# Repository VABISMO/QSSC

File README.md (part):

# QSSC — Quantum Solid State Chip 
## Open Source Quantum Computer

A room-temperature **solid-state spin-defect** quantum platform: a Qiskit
backend, an FPGA control stack with PCB design, a validated chip-fabrication
protocol, and a web dashboard.

The qubits are **spins in NV⁻ centres in CVD diamond**, coupled by magnetic
dipole and driven by microwaves. The device operates at **~300 K** with
benchtop electronics: zero-field splitting D ≈ 2.87 GHz, ODMR readout,
64 parallel emitter and detector channels on a 20×20 mm die.

> Solid-state spin defects (NV-diamond, hBN V_B⁻, SiC V_Si) keep quantum
> coherence at **~300 K**, so the chip does not require a dilution refrigerator.
> The canonical **default** defect is the **nitrogen-vacancy (NV⁻) centre in
> CVD diamond** — the only family here whose room-temperature coherence
> (**T₂ ≈ 1.8 ms** in ¹²C-enriched diamond) is long enough to *compute*
> seriously at 300 K. Zero-field splitting **D ≈ 2.87 GHz**, room-temperature
> ODMR readout. hBN V_B⁻ and SiC V_Si are retained as **sensor variants**.

## What's in the box

| Layer | Where | Description |
|---|---|---|
| **Python core** | `qssc/` | `QSSCBackend` (Qiskit `BackendV2`), simulator, defect profiles, quantum circuits, fabrication-protocol model |
| **REST backend** | `api/` | FastAPI app exposing the simulator, ODMR model, protocol and a circuit runner |
| **Frontend** | `frontend/` | React 18 + Vite dashboard (ODMR chart, qubit grid, circuit runner, protocol viewer) |
| **FPGA RTL** | `fpga/rtl` | 11 Verilog modules (Artix-7) — UART, SPI/ADF4351 PLL, 64-ch CQD emitter drive (3× TLC5947 + `dac_ctrl` gradient DAC), detector readout (TLV9004 TIA → 4× AD7616 parallel 16-bit ADC, 1 kHz lock-in host-side), hardware QRNG (`qrng_entropy` von-Neumann extractor), command parser, top-level |
| **Hardware** | `hardware/` | KiCad boards (main control + detector head — the two sandwich boards), XDC constraints, CNC G-code, datasheets, `HARDWARE_DESIGN.md` |
| **Protocol** | `docs/FABRICATION_PROTOCOL_Diamond.md` | NV-diamond fabrication protocol: CQD emitter array, CVD diamond + NV⁻ defect engineering, on-chip photodetectors, assembly, safety |
| **Tests** | `tests/` | software/physics tests (defects, simulator, circuits, backend, API, crypto, cross-platform) — **1202 collected**, of which 1149 run in CI — plus a PCB gate track (DRC, connectivity, pin audit, routing, board integrity) that runs locally against an installed KiCad |

## Quick start

```bash
# clone, then work from the repository root (pyproject.toml lives there;
# qssc/ is the package, not a directory you cd into)
python -m venv .venv && . .venv/bin/activate
pip install -e ".[api,dev,hw]"

# run the test suite
python -m pytest --ignore-glob='tests/test_pcb_*'
#   1090 passed, 59 skipped  (see ## Testing)

# try the CLI
qssc info                              # backend / defect summary (defaults to NV)
qssc shor 15                           # → factors 3 × 5
qssc odmr                              # ODMR spectrum (NV default, dip at 2.87 GHz)

# start the REST backend (port 8011 matches the Vite dev proxy + api/main.py
# default; the Dockerfile uses PORT env, default 8000, for deploy)
uvicorn api.main:app --port 8011

# in another shell, the dashboard
cd frontend
npm install && npm run dev             # http://localhost:5173
```

## Defect platforms

| Platform | Defect | D (GHz) | T₂ @ 300 K | Readout err | Excitation | Role |
|---|---|---|---|---|---|---|
| **Diamond** | **NV⁻ (nitrogen-vacancy)** | **2.87** | **~1.8 ms\*** | **8 %** | **532 nm (green)** | **default / compute** |
| hBN | V_B⁻ (boron-vacancy) | 3.46 | ~2 µs | 12 % | 561 nm | sensor variant |
| SiC | V_Si (silicon vacancy) | 0.07 / 0.14 | ~40 µs | ~15 % | 780 nm | sensor variant |

\* The 1.8 ms **compute** figure is specific to a **bulk ¹²C-enriched CVD
diamond** plate (Balasubramanian 2009: T₂ ≈ 1.8 ms, T₁ ≈ 6 ms at 300 K;
single-qubit gate ~25 ns, two-qubit gate ~200 ns, readout ~3 µs) — long enough
to compute at room temperature. The as-built lab route instead spin-coats
**microdiamond** powder onto the carrier: those µm-scale grains host NV
ensembles with µs–tens-of-µs T₂, so the microdiamond layer is a **sensor
array**, not a compute substrate. The compute claim is scoped to the bulk-CVD
material route; both routes share the canonical 20×20 mm two-faced die (see
*Chip architecture*). hBN V_B⁻ and SiC V_Si are likewise **sensor variants**
(their T₂ is too short for serious compute at 300 K, but they sense well).

## Chip architecture

The **canonical chip is a 20×20 mm two-faced die** — 130 bond pads on a 2.5 mm
pitch (65 pads per face: 64 electrodes in an 8×8 grid + 1 common), with **no
through-silicon vias**: the emitter face and the detector face are independent
surfaces on opposite sides of the bare die. The two-board PCB sandwich (a
150×118 mm main board + a 110×102 mm head board, 6 layers each) is built
around that die — the emitter face sits in a plain through-hole 2.54 mm socket
on the main board (die removable) and the detector face plugs into the head
board's matching through-hole socket; the main board carries the FPGA, the
AD7616 readout and the TLC5947 emitter drivers. Everything below is
specified relative to that canonical die.

The chip integrates its own emitter and detector arrays and is read
**electrically**: photocurrent → transimpedance amplifier → ADC. The 64 CQD emitters (driven in
parallel by 3× TLC5947 constant-current drivers) pump the NV⁻ ensemble
(green ~520–540 nm); a resonant microwave X-gate
(2.87 GHz) flips the spin to the dark ms=±1 state; the on-chip
graphene/MoS₂ detector array measures the resulting photocurrent dip
(ODMR). A 650 nm long-pass filter blocks the green pump and passes the NV
PL (637–800 nm). Each detector electrode feeds a **TLV9004 transimpedance
amplifier** (16× quad chips), and **4× AD7616 16-bit ADCs** digitise all 64
channels (codes 0–65535) over a **9-wire SPI** bus, with **1 kHz lock-in**
demodulation host-side.

```mermaid
flowchart TB
  classDef layer fill:#16203f,stroke:#263056,color:#cfe
  classDef flow fill:#0c1430,stroke:#1d2748,color:#9fb
  classDef mw fill:#2a1530,stroke:#4a2a55,color:#f9a
  classDef elec fill:#102018,stroke:#1f4a2a,color:#9fe

  EM["**64 parallel CQD emitters (3× TLC5947)** — ITO/PEDOT:PSS/CQD-PVA/ZnO/Ag, 520–540 nm"]:::layer
  HOST["**CVD diamond spin-defect host** — NV⁻, D ≈ 2.87 GHz, T₂ ≈ 1.8 ms"]:::layer
  FILT["**650 nm long-pass filter** — blocks green pump, passes NV PL"]:::layer
  DET["**Graphene / MoS₂ photodetector array** — 64 electrodes, bias 0.1–1 V"]:::layer

  EM -- "green pump 520–540 nm (↑)" --> HOST
  HOST -- "NV PL 637–800 nm (↑)" --> FILT
  FILT -- "passes PL, blocks pump" --> DET
  DET -- "photocurrent (↓)" --> TIA["**TLV9004 TIA ×16**"]:::elec
  TIA --> ADC["**4× AD7616 16-bit ADC · 1 kHz lock-in (host)**"]:::elec
  ADC --> CTRL["**Artix-7 control FPGA** (`fpga/rtl`) — emitters, SPI, lock-in"]:::elec

  MW["**ADF4351 MW · 2.87 GHz**"]:::mw
  MW -. "resonant X-gate (phase ≈ π) → ms=±1 dark" .-> HOST
  DET -. "ODMR dip = reduced photocurrent → bit 1" .-> ADC
```

Readout: a pumped site with **no** resonant MW reads **bright** (high ADC
code, bit 0); a resonant X-gate flips the spin to **dark** (low ADC code,
ODMR dip, bit 1). Calibration drives each emitter pixel and reads all
detectors to build the emitter-pixel → detector-electrode LUT — no jig.

## Qiskit backend

`qssc.backend.QSSCBackend` is a real `BackendV2` subclass with a `Target`,
`CouplingMap`, `QubitProperties` and per-site `InstructionProperties`.
Circuits run through Qiskit Aer and return standard `get_counts()`.

Three noise modes (set via the backend `noise_mode` option):

- **`real`** (default) — the full physics path. For circuits with ≤ 10
  active qubits and no opaque compiled blocks it runs a full Aer
  density-matrix simulation with thermal + depolarizing + readout noise built
  from the defect's real T₁/T₂ and gate times (O(4ⁿ)). Larger or compiled-block
  circuits fall back to the **analytic decoherence limit** computed from the
  *same* real T₂ and gate-time parameters plus **cumulative per-gate
  depolarization**. A shared
  `signal_retention = exp(−t/T₂)·(1−d₁q)^n₁q·(1−d₂q)^n₂q`
  metric drives both the assessment and the analytic blend, so a 13-qubit Shor
  run on NV at 300 K retains ~4.7 % of the *spin* signal and still recovers the
  factors (3, 5) — NV computes at room temperature; cooling to 1 mK lifts
  retention only to ~5.5 % because NV is
  depolarization-limited, not coherence-limited.
- **`phenomenological`** (fast analytic approximation) — ideal Aer statevector +
  post-hoc per-site readout bit-flip + the same coherence×depolarization
  damping blended into the distribution. O(n) in qubits; runs in milliseconds.
- **`none`** (ideal) — noiseless statevector only.

`aer` is accepted as an alias of `real`. The phenomenological and real modes
share the *same* real T₂/gate-time parameters, so their coherence verdicts
agree — only the granularity of the noise differs.

**On-chip 2-qubit gate = spin gate (room-temperature entanglement).** The QSSC
entangles qubits with a **~200 ns microwave / magnetic-dipole spin gate**.
Spin entanglement at room temperature is documented for NV
(Neumann 2008 — electron↔nucleus; Dolde 2013 — two NV electron spins via
dipole-dipole, *Nature Physics* 9:139). Because NV's spin T₂ ≈ 1.8 ms at 300 K
≫ the 200 ns gate, the on-chip 2q gate works at room temperature and NV **computes
at 300 K** (a 13-qubit Shor-15 recovers (3, 5); a Bell pair keeps its |00⟩+|11⟩
correlations). hBN (T₂ ~ 2 µs) and SiC (~ 40 µs) are sensor variants — shallow
circuits work at 300 K, deep ones (Shor) do not. The gate fidelity is governed
by the spin T₁/T₂ + depolarization budget above (`signal_retention`).

**Per-pixel NV register (within-pixel all-to-all dipole).** The 2q gate is a
*within one microdiamond* interaction: each of the 64 die pixels holds a small
(~10 NV) register, the NVs a few nm apart, so the 1/r³ dipole couples every pair
(complete graph K_n, ODMR-frequency-addressed by one global MW antenna). The
qiskit backend (`qssc/backend.py`) simulates ONE pixel's ~10-NV register as its
circuit qubits (64×10 = 640 exceeds the 63-qubit MPS cap, so the 64 pixels are
modelled as 64 **independent** parallel processors at 300 K). Cross-pixel
coupling at the 2.5 mm pixel pitch is negligible at 300 K, so the design treats
the die as 64 independent registers. The 64-pixel hardware die (the detector
array, `/api/calibration`, the FPGA 64-channel RTL) is unchanged — `num_qubits`
≈ 10 (the register) and `pixels` = 64 (the die) now diverge. The dipole physics
is grounded in `qssc/dipole.py` (CZ gate time, addressing leakage, fidelity).

Algorithms included: **Shor** (QPE period finding), **period finding**,
**Grover search**, **Bell/GHZ**, and **quantum arithmetic** (add / sub / mul /
sqrt / log via Draper QFT adder, RGQFT multiplier and phase estimation).

### Custom Qiskit circuits

Beyond the demo algorithms, the dashboard and API accept a **user-supplied
Qiskit circuit** — either an **OpenQASM 2** string or a **Python snippet** that
builds a `QuantumCircuit` named `qc`. The builder (`qssc.build_user_circuit`)
runs the snippet in a restricted namespace (imports limited to
`qiskit` / `numpy` / `math`, no file/network/process access) and caps the
circuit at 64 qubits.

```bash
# API
curl -X POST localhost:8011/api/circuit/custom \
  -H 'Content-Type: application/json' \
  -d '{"code":"from qiskit import QuantumCircuit\nqc=QuantumCircuit(3,3)\nqc.h(0);qc.cx(0,1);qc.cx(1,2);qc.measure(range(3),range(3))","shots":512}'
```

In the dashboard, select algorithm **custom** to get a code editor with
ready-made Bell / GHZ / QFT / QASM examples.

> Security note: this is intended for a **local lab / demo tool**, not a public
> multi-tenant service. The sandbox is a restricted namespace, not a hardened
> isolation boundary.

### Environment variables

Operator-facing knobs read by the REST backend and its guards. Defaults are
what the code falls back to when the variable is unset.

| Variable | Default | Effect |
|---|---|---|
| `QSSC_API_PORT` | `8011` | Port for `uvicorn` when running `python -m api.main` directly (the Dockerfile uses `PORT`, default 8000). |
| `QSSC_RATE_LIMIT_PER_MIN` | `20` | Per-IP request budget per minute; over-budget callers get 429. |
| `QSSC_ALLOW_SYNC` | *(off)* | Set `1`/`true` to allow `?sync=true` from non-localhost. Off by default: a synchronous run blocks the single uvicorn worker (DoS vector). |
| `QSSC_TRUSTED_PROXY_CIDR` | *(empty)* | If set (e.g. `10.0.0.0/8`), the immediate peer is treated as a reverse proxy and the client IP is taken from `X-Forwarded-For`. Empty = every request is judged by its TCP peer only. |
| `QSSC_CORS_ORIGINS` | `*` | Allowed CORS origins (comma-separated for multiple). |
| `QSSC_ENABLE_CUSTOM_CIRCUIT` | `1` | `0` disables the user-supplied Qiskit-circuit endpoint (503). |
| `QSSC_CUSTOM_API_KEY` | *(empty)* | When set, `POST /api/circuit/custom` requires a matching `X-API-Key` header (401 otherwise); empty = open. |
| `QSSC_TESTING` | *(unset)* | Set to `1` by the test suite so the `TestClient` pseudo-peer counts as localhost; **leave unset in production.** |
| `QSSC_FPGA_PORT` | *(unset)* | UART device for the real board (e.g. `/dev/ttyUSB0`); unset = the stack falls back to the simulator. |
| `QSSC_FPGA_PROFILE` | `NV` | Simulation profile for the fallback `SimulatedFPGA` when no board is present. |
| `QSSC_SEED` | `42` | Seed for the simulated-FPGA RNG (reproducible sim runs). |

> The PCB-generation overrides — `QSSC_ZONE_CLEARANCE_NM`,
> `QSSC_ZONE_MIN_WIDTH_NM`, `QSSC_VIA_DIAM_NM`, `QSSC_VIA_DRILL_NM`,
> `QSSC_COPPER_GAP_NM`, `QSSC_ROUTE_DEBUG`, `QSSC_RAIL_MICRO`,
> `QSSC_STITCH_STEP`, `QSSC_PCB_PATH` — are development-time router settings
> read by `tools/route_qssc_pcb.py` and `tools/router/*` (the pour and rail
> overrides are described in
> [`hardware/HARDWARE_DESIGN.md`](hardware/HARDWARE_DESIGN.md)).

## FPGA control stack

A single **Artix-7 XC7A35T-1CSG324C** orchestrates **64 individual on-chip CQD
ASE/LED emitters** (green ~520–540 nm, constant-current-driven by 3× TLC5947
PWM drivers off a +12 V emitter rail), the **on-chip graphene/MoS₂ photodetector
array** read through 16× TLV9004 TIAs into **4× AD7616 parallel 16-bit ADCs**
with **1 kHz lock-in** demodulation host-side, an **ADF4351** microwave PLL, and
a host UART link. The chip integrates its own emitter and detector arrays and is
read electrically: the ODMR dip is a reduction of photocurrent at resonance.
The RTL ([`fpga/rtl/`](fpga/rtl), 11 modules + a self-checking
[testbench](fpga/sim/tb_top_level.v)) is **parse-verified with pyverilog,
functionally simulated with iverilog, and synthesised with yosys
`synth_xilinx` (xc7, `-abc9` pinned)** — the testbench drives
`DRIVE_EMITTER 3 100` (fires one emitter + `OK` reply),
`READ_RNG 4` (asserts the 8-hex-digit debiased word + the
`" 00064 0 0"` raw-sample stats footer) and
`READ_DETECTORS` (asserts the 64-sample stream `1234 1234 … 1234\n`,
320 bytes, 19/19 checks pass). The yosys synthesis maps the design to the
Series-7 cell library and confirms it fits the XC7A35T-1CSG324C
(**8377 LUT / 40.3 %, 7442 FF / 17.9 %, 1313 CARRY4 / 25.2 %, 9 DSP48E1 /
10.0 %, 0 inferred latches, 0 blackboxes**, 18528 tech-mapped cells — the
committed numbers live in [`fpga/synth/SYNTH_REPORT.md`](fpga/synth/SYNTH_REPORT.md)).
Synthesis runs the **staged** tree — `fpga/rtl` passed through the same patch
chain the Vivado build applies ([`fpga/synth/stage_rtl.py`](fpga/synth/stage_rtl.py)) —
so the gate measures the configuration that ships. Those three checks run in CI
**whenever `fpga/**` changes** (the FPGA job is
path-filtered: a full yosys run costs ~45 min) and locally with
`bash fpga/synth/run_synth.sh`. (A first iverilog
run caught two real handshake bugs pyverilog could not — a readout busy race and
a missing consumer-ack — now fixed.) Pin assignments live in
[`fpga/constraints.xdc`](fpga/constraints.xdc); the synthesis flow + report
live in [`fpga/synth/`](fpga/synth) (see
[`hardware/HARDWARE_DESIGN.md`](hardware/HARDWARE_DESIGN.md) §17).

### Boards

The same RTL drives both board variants — the readout goes to an external AD7616
over SPI, so nothing depends on the Xilinx XADC hard block, and only the `.xdc`
pin map changes. Toolchain for both is the free Xilinx **Vivado**; the host link
is a USB cable to the board's USB-UART bridge at **115200-8-N-1**.

| Variant | FPGA | Where | Status |
|---|---|---|---|
| **Custom QSSC PCB** | Artix-7 **XC7A35T-1CSG324C** | [`hardware/pcb/`](hardware/pcb), pins in [`fpga/constraints.xdc`](fpga/constraints.xdc) | design artefact: boards, XDC and yosys synthesis complete; bitstream packaging outstanding |
| **Home-lab QMTECH** | Artix-7 **XC7A15T** (stock dev board) | [`fpga/qmtech/`](fpga/qmtech) | **verified on hardware**: bitstream built and flashed, JTAG reports `init 1 done 1` |

- **QMTECH (home lab):** `bash fpga/qmtech/build.sh`, then
  `bash fpga/qmtech/flash_qmtech.sh`. Wiring: [`fpga/INTERCONNECT.md`](fpga/INTERCONNECT.md);
  pin map: [`fpga/qmtech/PINMAP.md`](fpga/qmtech/PINMAP.md).
- **Custom QSSC PCB:** JTAG through a Digilent JTAG-HS3 or Xilinx Platform Cable
  USB II into the 6-pin header (`TCK=E10 TMS=E12 TDI=E11 TDO=E13`), UART through
  the on-board FT232RL. The Digilent Arty A7-35T and Cmod A7-35T also run this
  firmware with a remapped pin file ([`HARDWARE_DESIGN.md`](hardware/HARDWARE_DESIGN.md) §1A).

The host protocol is a small ASCII UART command set (115200 baud, 8-N-1,
`\n`-terminated; all numbers decimal integers — see
[`hardware/HARDWARE_DESIGN.md`](hardware/HARDWARE_DESIGN.md) §5 for the full
specification):

| Command | Action | Reply |
|---|---|---|
| `DRIVE_EMITTER <index> <duration_ms>` | fire emitter `<index>` (0–63) | `OK` |
| `APPLY_PULSE <qubit> <freq_khz> <amp> <duration_ns> <phase>` | program ADF4351 + gate the MW pulse | `OK` |
| `READ_DETECTOR <site>` | digitise one detector electrode (AD7616) | `<code>` |
| `READ_DETECTORS` | sweep all 64 electrodes, stream codes | `<code> <code> …` (64) |
| `CALIBRATE` | drive each emitter + read detectors, build emitter→detector LUT | `OK` |

`freq_khz` is the RF carrier in kHz (e.g. `2870000` for 2.87 GHz NV⁻, `3460000`
for 3.46 GHz hBN V_B⁻); the pulse is split across the ADF4351 and the RF switch:
`freq_khz` → PLL carrier, `phase` (milliradians) → R1 PHASE register, `amp` 0–3
→ R4 RF_PWR output-power index, `duration_ns` → the `mw_gate` RF-switch pin (a
gate timer counts `duration_ns/10` cycles at 100 MHz). The FPGA does not shape
the analog envelope — an external AWG/modulator does. Detector codes are 16-bit
ADC values (0–65535, AD7616). The Python [`EmitterController`](qssc/backend.py) /
[`DetectorInterface`](qssc/backend.py) /
[`MicrowaveController`](qssc/backend.py) emit exactly this integer form, so the
same control code drives the [`SimulatedFPGA`](qssc/simulator.py) and a real
board.

### Connecting the board + flashing the firmware

**Hardware.** Target FPGA: **Artix-7 XC7A35T-1CSG324C** on the custom QSSC
PCB (the same RTL also runs on a Digilent Arty A7-35T / Cmod A7-35T — only the
`.xdc` pin map changes; see [`HARDWARE_DESIGN.md`](hardware/HARDWARE_DESIGN.md)
§1A). Two cables:

1. **JTAG** — to flash the bitstream. Use a **Digilent JTAG-HS3** or **Xilinx
   Platform Cable USB II** into the board's 6-pin JTAG header
   (`TCK=E10 TMS=E12 TDI=E11 TDO=E13`, see
   [`fpga/constraints.xdc`](fpga/constraints.xdc)). On an Arty A7, the on-board
   USB-JTAG does this — no separate cable.
2. **UART** — the host command link. A **USB-A → USB-B (or micro-USB) cable**
   to the board's USB-UART bridge (**FT232RL / FT2232H**), which enumerates as a
   serial port: `/dev/ttyUSB0` on Linux, `/dev/cu.usbserial-*` on macOS,
   `COM3` on Windows. Link is **115200 baud, 8-N-1, `\n`-terminated ASCII**.

**Host install (with the serial extra).** The base install has no pyserial; the
real-board path needs the optional `[hw]` extra:

```bash
pip install -e ".[hw]"      # pulls pyserial>=3.5
export QSSC_FPGA_PORT=/dev/ttyUSB0   # the UART port above
```

**Build the bitstream** (on a machine with Xilinx Vivado — Vivado is not in CI).
Synthesis is yosys; place-and-route + bitstream write need Vivado:

```bash
# 1. yosys synthesis -> fpga/synth/qssc_top.edif (runs headless, no Vivado)
cd fpga/synth && ./run_synth.sh

# 2. Vivado place-and-route + bitstream (batch Tcl)
vivado -mode batch -source - <<'TCL'
set part xc7a35tcsg324-1
read_edif qssc_top.edif
read_xdc ../constraints.xdc
link_design -part $part -top qssc_top
opt_design; place_design; route_design
report_timing_summary
write_bitstream -force qssc_top.bit
TCL
```

> The repo ships the already-synthesised `fpga/synth/qssc_top.edif`, so you can
> skip step 1 and go straight to Vivado with the EDIF + `fpga/constraints.xdc`.

**Flash.** Open Vivado **Hardware Manager**: *Open target → Auto-connect* (the
JTAG-HS3 / Platform Cable appears), *Program device → select qssc_top.bit*.
To boot from power-on without the cable, also write it to the on-board
**W25Q128 QSPI flash** (Vivado *Add configuration flash device →
write_bitstream* with the SPI config). Alternatively,
`openFPGALoader -b artix_a7_35t qssc_top.bit` works for the Arty A7.

**Verify the link.** With the board flashed and `QSSC_FPGA_PORT` set, start the
stack and probe:

```bash
uvicorn api.main:app --port 8011 &        # API
cd frontend && npm run dev &              # dashboard on :5173
.venv/bin/rq worker qssc --url redis://localhost:6379/0 &   # async job queue
curl localhost:8011/api/fpga/probe        # -> {"connected": true, "id": "QSSC v1", ...}
```

In the dashboard, switch the top-level toggle to **Hardware**: the indicator
turns green (*FPGA connected — QSSC v1 on /dev/ttyUSB0*). Run a circuit → the
result is labelled `source: hardware · I/O: real`. With **no board** (or
`QSSC_FPGA_PORT` unset), the same switch shows a red *No FPGA detected* banner
and never silently falls back to the simulator.

**Firmware status.** All 19 verbs are implemented in the RTL: `DRIVE_EMITTER`,
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
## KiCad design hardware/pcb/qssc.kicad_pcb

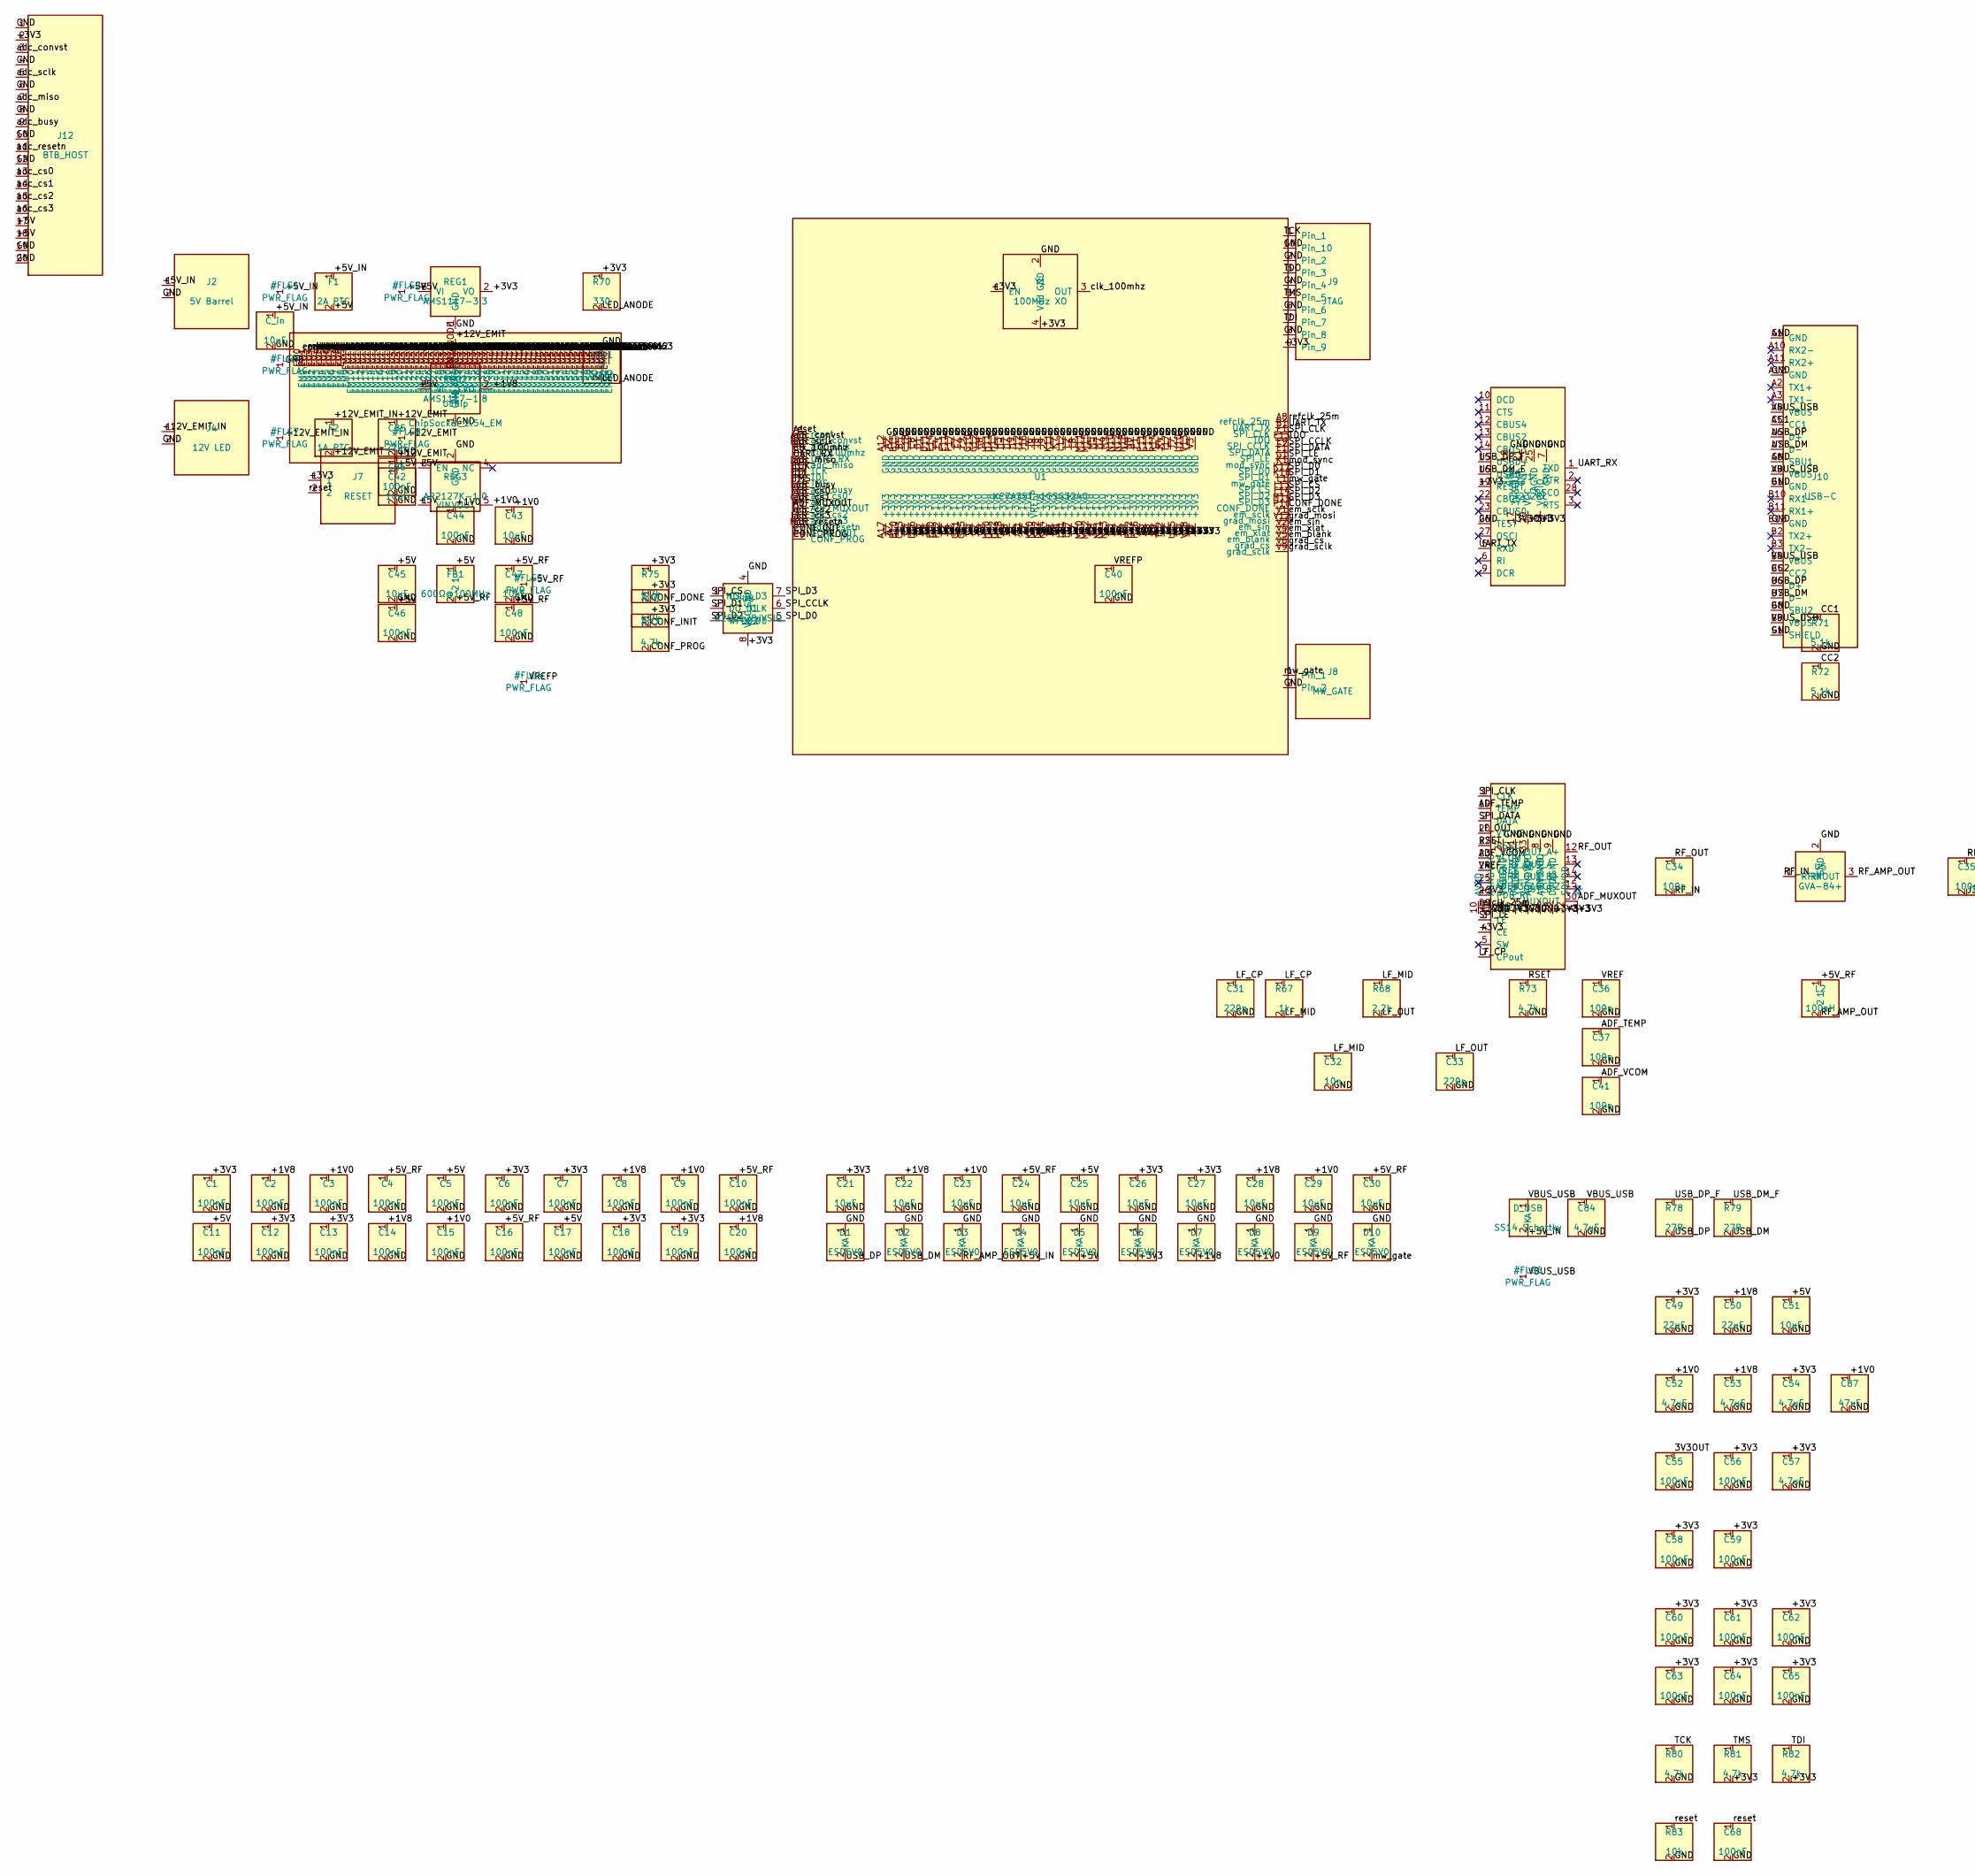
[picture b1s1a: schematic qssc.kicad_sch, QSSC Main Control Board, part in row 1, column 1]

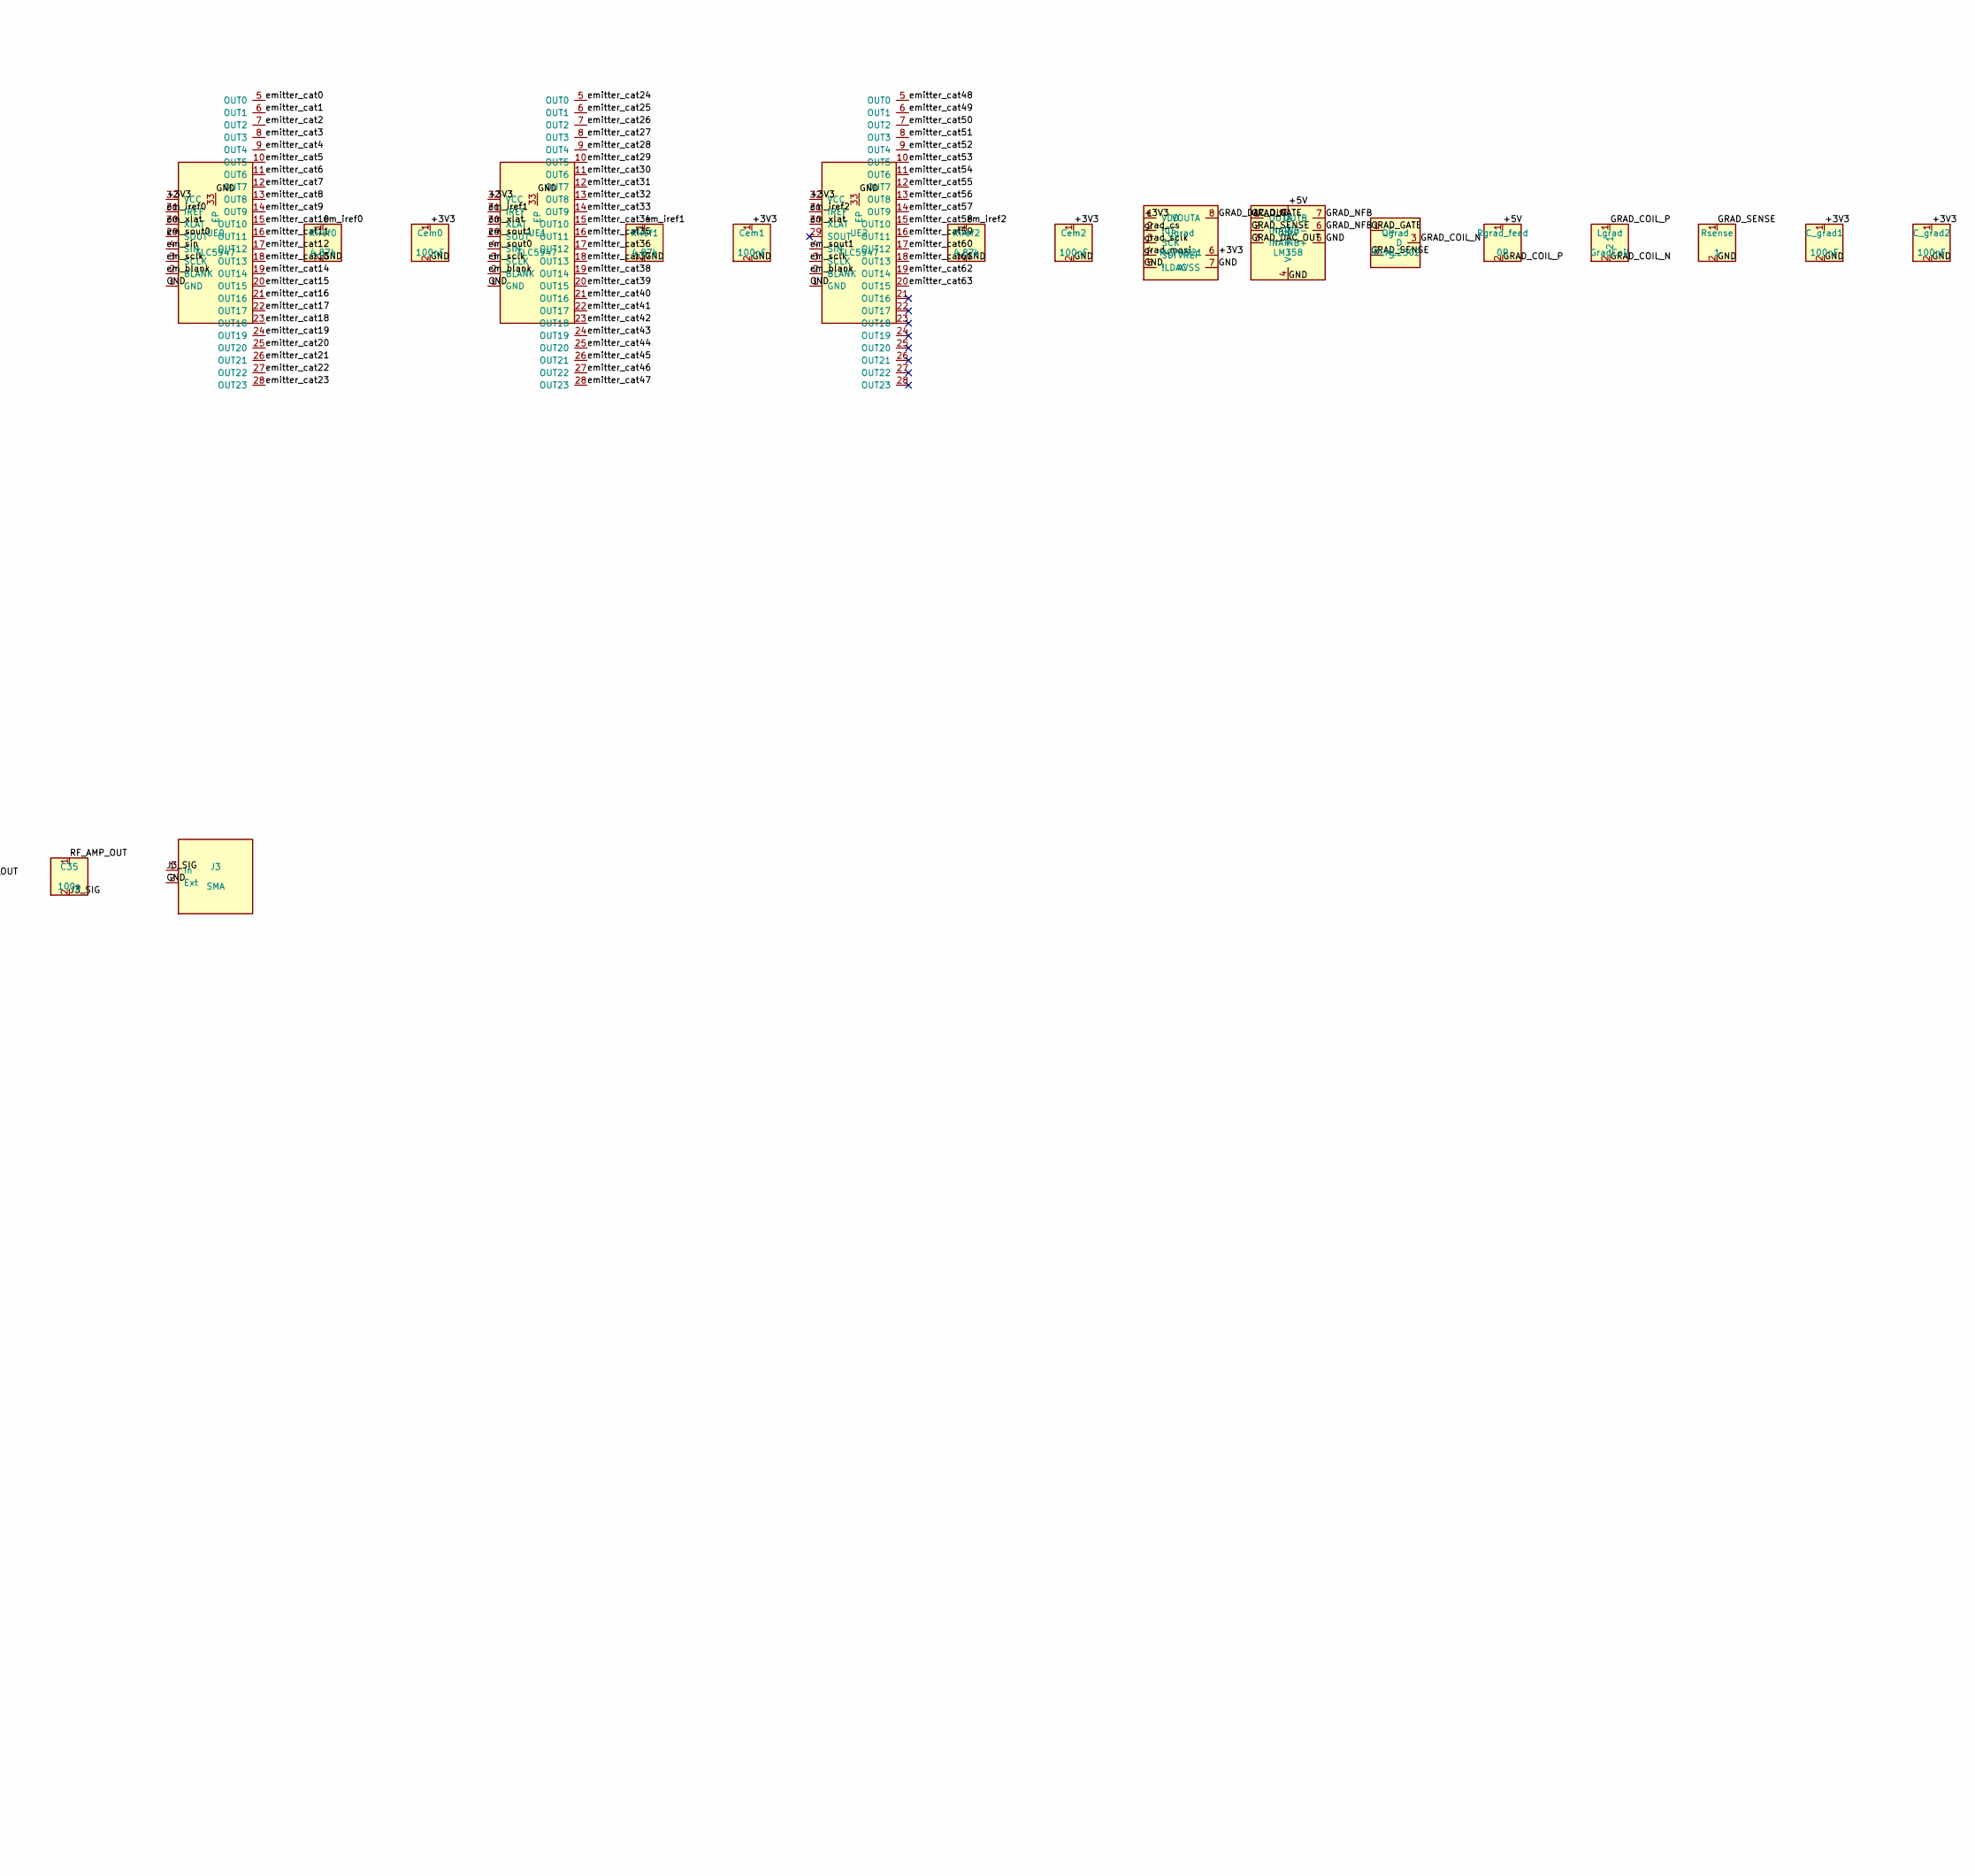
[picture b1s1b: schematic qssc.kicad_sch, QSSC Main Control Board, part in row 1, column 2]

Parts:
C1, C2, C3, C4, C5, C6, C7, C8, C9, C10, C11, C12, C13, C14, C15, C16, C17, C18, C19, C20, C40, C44, C46, C48, C55, C56, C58, C59, C60, C61, C62, C63, C64, C65, C68, C86: 100nF; C_0603_1608Metric
C21, C22, C23, C24, C25, C26, C27, C28, C29, C30, C42, C43, C45, C47, C51: 10uF; C_0805_2012Metric
C31, C33: 220p; C_0603_1608Metric
C32: 10n; C_0603_1608Metric
C34, C35: 100p; C_0603_1608Metric
C36, C37, C41: 100n; C_0603_1608Metric
C49, C50, C85: 22uF; C_0805_2012Metric
C52, C53, C54, C57, C84: 4.7uF; C_0805_2012Metric
C87: 47uF; C_1206_3216Metric
C_grad1, C_grad2: 100nF; C_0603_1608Metric
C_in: 10uF; C_0805_2012Metric
Cem0, Cem1, Cem2: 100nF; C_0603_1608Metric
D1, D2, D3, D4, D5, D6, D7, D8, D9, D10: ESD5V0; D_SOD-923
D_USB: SS14 Schottky; D_SMA
F1: 2A PTC; Fuse_1206_3216Metric
F2: 1A PTC; Fuse_1206_3216Metric
FB1: 600Ω@100MHz; L_0603_1608Metric
J1: FT232RL; SSOP-28_5.3x10.2mm_P0.65mm
J2: 5V Barrel; BarrelJack_CUI_PJ-102AH_Horizontal
J3: SMA; SMA_Amphenol_132289_EdgeMount
J4: 12V LED; BarrelJack_CUI_PJ-102AH_Horizontal
J7: RESET; SW_PUSH_6mm_H5mm
J8: MW_GATE; PinHeader_1x02_P2.54mm_Vertical
J9: JTAG; PinHeader_2x05_P2.54mm_Vertical
J10: USB-C; USB_C_Receptacle_GCT_USB4105-xx-A_16P_TopMnt_Horizontal
J12: BTB_HOST; Conn_02x10_BTB
L2: 100nH; L_0603_1608Metric
LED1: Green; LED_0603_1608Metric
Lgrad: GradCoil
Qgrad: IRLML2502; SOT-23-3
R67: 1k; R_0603_1608Metric
R68: 2.2k; R_0603_1608Metric
R70: 330; R_0603_1608Metric
R71, R72: 5.1k; R_0603_1608Metric
R73, R75, R76, R77, R80, R81, R82: 4.7k; R_0603_1608Metric
R78, R79: 27R; R_0603_1608Metric
R83: 10k; R_0603_1608Metric
REG1: AMS1117-3.3; SOT-223-3_TabPin2
REG2: AMS1117-1.8; SOT-223-3_TabPin2
REG3: AP2127K-1.0; SOT-23-5
Rgrad_feed: 0R; R_0805_2012Metric
Riref0, Riref1, Riref2: 4.87k; R_0603_1608Metric
Rsense: 1; R_2512_6332Metric
U1: XC7A35T-1CSG324C; Xilinx_CSG324
U3: ADF4351BCPZ; QFN-32-1EP_5x5mm_P0.5mm_EP3.45x3.45mm
U5: GVA-84+; SOT-89-3
U8: W25Q128JVSIQ; SOIC-8_3.9x4.9mm_P1.27mm
UE0, UE1, UE2: TLC5947; HTSSOP-32-1EP_6.1x11mm_P0.65mm_EP5.2x11mm_Mask4.11x4.36mm_T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
Uchip: ChipSocket_2.54_EM
Udrv: LM358; SOIC-8_3.9x4.9mm_P1.27mm
Ugrad: MCP4921; SOIC-8_3.9x4.9mm_P1.27mm
Y1: 100MHz XO; Oscillator_SMD_Abracon_ASE-4Pin_3.2x2.5mm

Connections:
3V3OUT: C55.1, J1.17 (3V3OUT)
+1V0: C3.1, C9.1, C15.1, C23.1, C29.1, C43.1, C44.1, C52.1, C87.1, D8.2 (A), REG3.5 (VOUT), U1.F8 (+1V0), U1.F10 (+1V0), U1.G7 (+1V0), U1.G9 (+1V0), U1.G11 (+1V0), U1.H8 (+1V0), U1.J7 (+1V0), U1.J11 (+1V0), U1.K8 (+1V0), U1.L7 (+1V0), U1.L11 (+1V0), U1.M8 (+1V0), U1.M10 (+1V0), U1.N7 (+1V0), U1.N9 (+1V0), U1.N11 (+1V0)
+1V8: C2.1, C8.1, C14.1, C20.1, C22.1, C28.1, C50.1, C53.1, D7.2 (A), REG2.2 (VO), U1.F12 (+1V8), U1.H10 (+1V8), U1.H12 (+1V8), U1.K12 (+1V8), U1.M12 (+1V8)
+3V3: C1.1, C6.1, C7.1, C12.1, C13.1, C18.1, C19.1, C21.1, C26.1, C27.1, C49.1, C54.1, C56.1, C57.1, C58.1, C59.1, C60.1, C61.1, C62.1, C63.1, C64.1, C65.1, C_grad1.1, C_grad2.1, Cem0.1, Cem1.1, Cem2.1, D6.2 (A), J1.4 (VCCIO), J1.19 (~RESET), J1.20 (VCC), J7.1, J9.9, J12.2, R70.1, R75.1, R76.1, R77.1, R81.2, R82.2, REG1.2 (VO), U1.A7 (+3V3), U1.A17 (+3V3), U1.B10 (+3V3), U1.C3 (+3V3), U1.C13 (+3V3), U1.D6 (+3V3), U1.D16 (+3V3), U1.E8 (+3V3), U1.F2 (+3V3), U1.G5 (+3V3), U1.G15 (+3V3), U1.H18 (+3V3), U1.J1 (+3V3), U1.K4 (+3V3), U1.K14 (+3V3), U1.L17 (+3V3), U1.N3 (+3V3), U1.N13 (+3V3), U1.P6 (+3V3), U1.P8 (+3V3), U1.P12 (+3V3), U1.P16 (+3V3), U1.R9 (+3V3), U1.T2 (+3V3), U1.T12 (+3V3), U1.U5 (+3V3), U1.U15 (+3V3), U1.V8 (+3V3), U1.V18 (+3V3), U3.4 (CE), U3.6 (Vp), U3.10 (AVDD), U3.16 (VVCO), U3.17 (VVCO), U3.26 (PDB_RF), U3.28 (DVDD), U3.32 (SDVDD), U8.8 (VCC), UE0.32 (VCC), UE1.32 (VCC), UE2.32 (VCC), Ugrad.1 (VDD), Ugrad.6 (VREF), Y1.1 (EN), Y1.4 (Vdd)
+5V: C5.1, C11.1, C17.1, C25.1, C42.1, C45.1, C46.1, C51.1, D5.2 (A), F1.2, FB1.1, J12.17, J12.18, REG1.3 (VI), REG2.3 (VI), REG3.1 (VIN), REG3.3 (EN), Rgrad_feed.1, Udrv.8 (V+)
+5V_IN: C_in.1, D4.2 (A), D_USB.2 (A), F1.1, J2.1
+5V_RF: C4.1, C10.1, C16.1, C24.1, C30.1, C47.1, C48.1, D9.2 (A), FB1.2, L2.1
+12V_EMIT: C85.1, C86.1, F2.2, Uchip.EM_ANODE
+12V_EMIT_IN: F2.1, J4.1
ADF_MUXOUT: U1.H1 (ADF_MUXOUT), U3.30 (MUXOUT)
ADF_TEMP: C37.1, U3.19 (TEMP)
ADF_VCOM: C41.1, U3.23 (VCOM)
CC1: J10.A5 (CC1), R71.1
CC2: J10.B5 (CC2), R72.1
CONF_DONE: R75.2, U1.P10 (CONF_DONE)
CONF_INIT: R76.2, U1.P7 (CONF_INIT)
CONF_PROG: R77.2, U1.P9 (CONF_PROG)
GND: C1.2, C2.2, C3.2, C4.2, C5.2, C6.2, C7.2, C8.2, C9.2, C10.2, C11.2, C12.2, C13.2, C14.2, C15.2, C16.2, C17.2, C18.2, C19.2, C20.2, C21.2, C22.2, C23.2, C24.2, C25.2, C26.2, C27.2, C28.2, C29.2, C30.2, C31.2, C32.2, C33.2, C36.2, C37.2, C40.2, C41.2, C42.2, C43.2, C44.2, C45.2, C46.2, C47.2, C48.2, C49.2, C50.2, C51.2, C52.2, C53.2, C54.2, C55.2, C56.2, C57.2, C58.2, C59.2, C60.2, C61.2, C62.2, C63.2, C64.2, C65.2, C68.2, C84.2, C85.2, C86.2, C87.2, C_grad1.2, C_grad2.2, C_in.2, Cem0.2, Cem1.2, Cem2.2, D1.1 (K), D2.1 (K), D3.1 (K), D4.1 (K), D5.1 (K), D6.1 (K), D7.1 (K), D8.1 (K), D9.1 (K), D10.1 (K), J1.7 (GND), J1.18 (GND), J1.21 (GND), J1.25 (AGND), J1.26 (TEST), J2.2, J3.2 (Ext), J4.2, J8.2, J9.2, J9.4, J9.6, J9.8, J9.10, J10.A1 (GND), J10.A8 (SBU1), J10.A12 (GND), J10.B1 (GND), J10.B8 (SBU2), J10.B12 (GND), J10.S1 (SHIELD), J12.1, J12.4, J12.6, J12.8, J12.10, J12.12, J12.19, J12.20, LED1.1 (K), R71.2, R72.2, R73.2, R80.2, R83.2, REG1.1 (GND), REG2.1 (GND), REG3.2 (GND), Riref0.2, Riref1.2, Riref2.2, Rsense.2, U1.A2 (GND), U1.A12 (GND), U1.B5 (GND), U1.B15 (GND), U1.C8 (GND), U1.C18 (GND), U1.D1 (GND), U1.D11 (GND), U1.E4 (GND), U1.E14 (GND), U1.F7 (GND), U1.F9 (GND), U1.F11 (GND), U1.F17 (GND), U1.G8 (GND), U1.G10 (GND), U1.G12 (GND), U1.H3 (GND), U1.H7 (GND), U1.H9 (GND), U1.H11 (GND), U1.H13 (GND), U1.J6 (GND), U1.J8 (GND), U1.J9 (GND), U1.J12 (GND), U1.J16 (GND), U1.K7 (GND), U1.K11 (GND), U1.L2 (GND), U1.L8 (GND), U1.L12 (GND), U1.M5 (GND), U1.M7 (GND), U1.M9 (GND), U1.M11 (GND), U1.M15 (GND), U1.N8 (GND), U1.N10 (GND), U1.N12 (GND), U1.N18 (GND), U1.P1 (GND), U1.P11 (GND), U1.P13 (GND), U1.R4 (GND), U1.R14 (GND), U1.T7 (GND), U1.T17 (GND), U1.U10 (GND), U1.V3 (GND), U1.V13 (GND), U3.8 (CPGND), U3.9 (AGND), U3.11 (AGNDVCO), U3.18 (AGNDVCO), U3.21 (AGNDVCO), U3.27 (DGND), U3.31 (SDGND), U3.33 (EP), U5.2 (GND), U8.4 (GND), UE0.1 (GND), UE0.33 (EP), UE1.1 (GND), UE1.33 (EP), UE2.1 (GND), UE2.33 (EP), Udrv.4 (V-), Udrv.5 (INB+), Ugrad.5 (!LDAC), Ugrad.7 (AVSS), Y1.2 (GND)
GRAD_COIL_N: Lgrad.2, Qgrad.3 (D)
GRAD_COIL_P: Lgrad.1, Rgrad_feed.2
GRAD_DAC_OUT: Udrv.3 (INA+), Ugrad.8 (VOUTA)
GRAD_GATE: Qgrad.1 (G), Udrv.1 (OUTA)
GRAD_NFB: Udrv.6 (INB-), Udrv.7 (OUTB)
GRAD_SENSE: Qgrad.2 (S), Rsense.1, Udrv.2 (INA-)
J3_SIG: C35.2, J3.1 (In)
LED_ANODE: LED1.2 (A), R70.2
LF_CP: C31.1, R67.1, U3.7 (CPout)
LF_MID: C32.1, R67.2, R68.1
LF_OUT: C33.1, R68.2, U3.20 (VTUNE)
RF_AMP_OUT: C35.1, D3.2 (A), L2.2, U5.3 (RFOUT)
RF_IN: C34.2, U5.1 (RFIN)
RF_OUT: C34.1, U3.12 (RF_OUT_A+)
RSET: R73.1, U3.22 (RSET)
SPI_CCLK: U1.E9 (SPI_CCLK), U8.6 (CLK)
SPI_CLK: U1.E1 (SPI_CLK), U3.1 (CLK)
SPI_CS: U1.L13 (SPI_CS), U8.1 (CS)
SPI_D0: U1.K17 (SPI_D0), U8.5 (DI_D0)
SPI_D1: U1.K18 (SPI_D1), U8.2 (DO_D1)
SPI_D2: U1.L14 (SPI_D2), U8.3 (WP_D2)
SPI_D3: U1.M14 (SPI_D3), U8.7 (HOLD_D3)
SPI_DATA: U1.F1 (SPI_DATA), U3.2 (DATA)
SPI_LE: U1.G1 (SPI_LE), U3.3 (LE)
TCK: J9.1, R80.1, U1.E10 (TCK)
TDI: J9.7, R82.1, U1.E11 (TDI)
TDO: J9.3, U1.E13 (TDO)
TMS: J9.5, R81.1, U1.E12 (TMS)
UART_RX: J1.1 (TXD), U1.C1 (UART_RX)
UART_TX: J1.5 (RXD), U1.B1 (UART_TX)
USB_DM: D2.2 (A), J10.A7 (D-), J10.B7 (D-), R79.2
USB_DM_F: J1.16 (USBD-), R79.1
USB_DP: D1.2 (A), J10.A6 (D+), J10.B6 (D+), R78.2
USB_DP_F: J1.15 (USBD+), R78.1
VBUS_USB: C84.1, D_USB.1 (K), J10.A4 (VBUS), J10.A9 (VBUS), J10.B4 (VBUS), J10.B9 (VBUS)
VREF: C36.1, U3.24 (VREF)
VREFP: C40.1, U1.K10 (VREFP)
adc_busy: J12.9, U1.E18 (adc_busy)
adc_convst: J12.3, U1.A18 (adc_convst)
adc_cs0: J12.13, U1.F18 (adc_cs0)
adc_cs1: J12.14, U1.G18 (adc_cs1)
adc_cs2: J12.15, U1.J18 (adc_cs2)
adc_cs3: J12.16, U1.L18 (adc_cs3)
adc_miso: J12.7, U1.D18 (adc_miso)
adc_resetn: J12.11, U1.M18 (adc_resetn)
adc_sclk: J12.5, U1.B18 (adc_sclk)
clk_100mhz: U1.B8 (clk_100mhz), Y1.3 (OUT)
em_blank: U1.V5 (em_blank), UE0.2 (BLANK), UE1.2 (BLANK), UE2.2 (BLANK)
em_iref0: Riref0.1, UE0.31 (IREF)
em_iref1: Riref1.1, UE1.31 (IREF)
em_iref2: Riref2.1, UE2.31 (IREF)
em_sclk: U1.V1 (em_sclk), UE0.3 (SCLK), UE1.3 (SCLK), UE2.3 (SCLK)
em_sin: U1.V2 (em_sin), UE0.4 (SIN)
em_sout0: UE0.29 (SOUT), UE1.4 (SIN)
em_sout1: UE1.29 (SOUT), UE2.4 (SIN)
em_xlat: U1.V4 (em_xlat), UE0.30 (XLAT), UE1.30 (XLAT), UE2.30 (XLAT)
emitter_cat0: UE0.5 (OUT0), Uchip.EM0
emitter_cat1: UE0.6 (OUT1), Uchip.EM1
emitter_cat2: UE0.7 (OUT2), Uchip.EM2
emitter_cat3: UE0.8 (OUT3), Uchip.EM3
emitter_cat4: UE0.9 (OUT4), Uchip.EM4
emitter_cat5: UE0.10 (OUT5), Uchip.EM5
emitter_cat6: UE0.11 (OUT6), Uchip.EM6
emitter_cat7: UE0.12 (OUT7), Uchip.EM7
emitter_cat8: UE0.13 (OUT8), Uchip.EM8
emitter_cat9: UE0.14 (OUT9), Uchip.EM9
emitter_cat10: UE0.15 (OUT10), Uchip.EM10
emitter_cat11: UE0.16 (OUT11), Uchip.EM11
emitter_cat12: UE0.17 (OUT12), Uchip.EM12
emitter_cat13: UE0.18 (OUT13), Uchip.EM13
emitter_cat14: UE0.19 (OUT14), Uchip.EM14
emitter_cat15: UE0.20 (OUT15), Uchip.EM15
emitter_cat16: UE0.21 (OUT16), Uchip.EM16
emitter_cat17: UE0.22 (OUT17), Uchip.EM17
emitter_cat18: UE0.23 (OUT18), Uchip.EM18
emitter_cat19: UE0.24 (OUT19), Uchip.EM19
emitter_cat20: UE0.25 (OUT20), Uchip.EM20
emitter_cat21: UE0.26 (OUT21), Uchip.EM21
emitter_cat22: UE0.27 (OUT22), Uchip.EM22
emitter_cat23: UE0.28 (OUT23), Uchip.EM23
emitter_cat24: UE1.5 (OUT0), Uchip.EM24
emitter_cat25: UE1.6 (OUT1), Uchip.EM25
emitter_cat26: UE1.7 (OUT2), Uchip.EM26
emitter_cat27: UE1.8 (OUT3), Uchip.EM27
emitter_cat28: UE1.9 (OUT4), Uchip.EM28
emitter_cat29: UE1.10 (OUT5), Uchip.EM29
emitter_cat30: UE1.11 (OUT6), Uchip.EM30
emitter_cat31: UE1.12 (OUT7), Uchip.EM31
emitter_cat32: UE1.13 (OUT8), Uchip.EM32
emitter_cat33: UE1.14 (OUT9), Uchip.EM33
emitter_cat34: UE1.15 (OUT10), Uchip.EM34
emitter_cat35: UE1.16 (OUT11), Uchip.EM35
emitter_cat36: UE1.17 (OUT12), Uchip.EM36
emitter_cat37: UE1.18 (OUT13), Uchip.EM37
emitter_cat38: UE1.19 (OUT14), Uchip.EM38
emitter_cat39: UE1.20 (OUT15), Uchip.EM39
emitter_cat40: UE1.21 (OUT16), Uchip.EM40
emitter_cat41: UE1.22 (OUT17), Uchip.EM41
emitter_cat42: UE1.23 (OUT18), Uchip.EM42
emitter_cat43: UE1.24 (OUT19), Uchip.EM43
emitter_cat44: UE1.25 (OUT20), Uchip.EM44
emitter_cat45: UE1.26 (OUT21), Uchip.EM45
emitter_cat46: UE1.27 (OUT22), Uchip.EM46
emitter_cat47: UE1.28 (OUT23), Uchip.EM47
emitter_cat48: UE2.5 (OUT0), Uchip.EM48
emitter_cat49: UE2.6 (OUT1), Uchip.EM49
emitter_cat50: UE2.7 (OUT2), Uchip.EM50
emitter_cat51: UE2.8 (OUT3), Uchip.EM51
emitter_cat52: UE2.9 (OUT4), Uchip.EM52
emitter_cat53: UE2.10 (OUT5), Uchip.EM53
emitter_cat54: UE2.11 (OUT6), Uchip.EM54
emitter_cat55: UE2.12 (OUT7), Uchip.EM55
emitter_cat56: UE2.13 (OUT8), Uchip.EM56
emitter_cat57: UE2.14 (OUT9), Uchip.EM57
emitter_cat58: UE2.15 (OUT10), Uchip.EM58
emitter_cat59: UE2.16 (OUT11), Uchip.EM59
emitter_cat60: UE2.17 (OUT12), Uchip.EM60
emitter_cat61: UE2.18 (OUT13), Uchip.EM61
emitter_cat62: UE2.19 (OUT14), Uchip.EM62
emitter_cat63: UE2.20 (OUT15), Uchip.EM63
grad_cs: U1.V6 (grad_cs), Ugrad.2 (!CS)
grad_mosi: U1.V12 (grad_mosi), Ugrad.4 (SDI)
grad_sclk: U1.V9 (grad_sclk), Ugrad.3 (SCK)
mod_sync: U1.K1 (mod_sync)
mw_gate: D10.2 (A), J8.1, U1.L1 (mw_gate)
refclk_25m: U1.A8 (refclk_25m), U3.29 (REFIN)
reset: C68.1, J7.2, R83.1, U1.A1 (reset)

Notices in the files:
README.md:
License:
Apache License 2.0 **with a non-commercial use restriction** — see
[`LICENSE`](LICENSE). Academic research, teaching and personal use are fine;
commercial use requires written permission from the author.
License: Apache-2.0 (non-commercial)
